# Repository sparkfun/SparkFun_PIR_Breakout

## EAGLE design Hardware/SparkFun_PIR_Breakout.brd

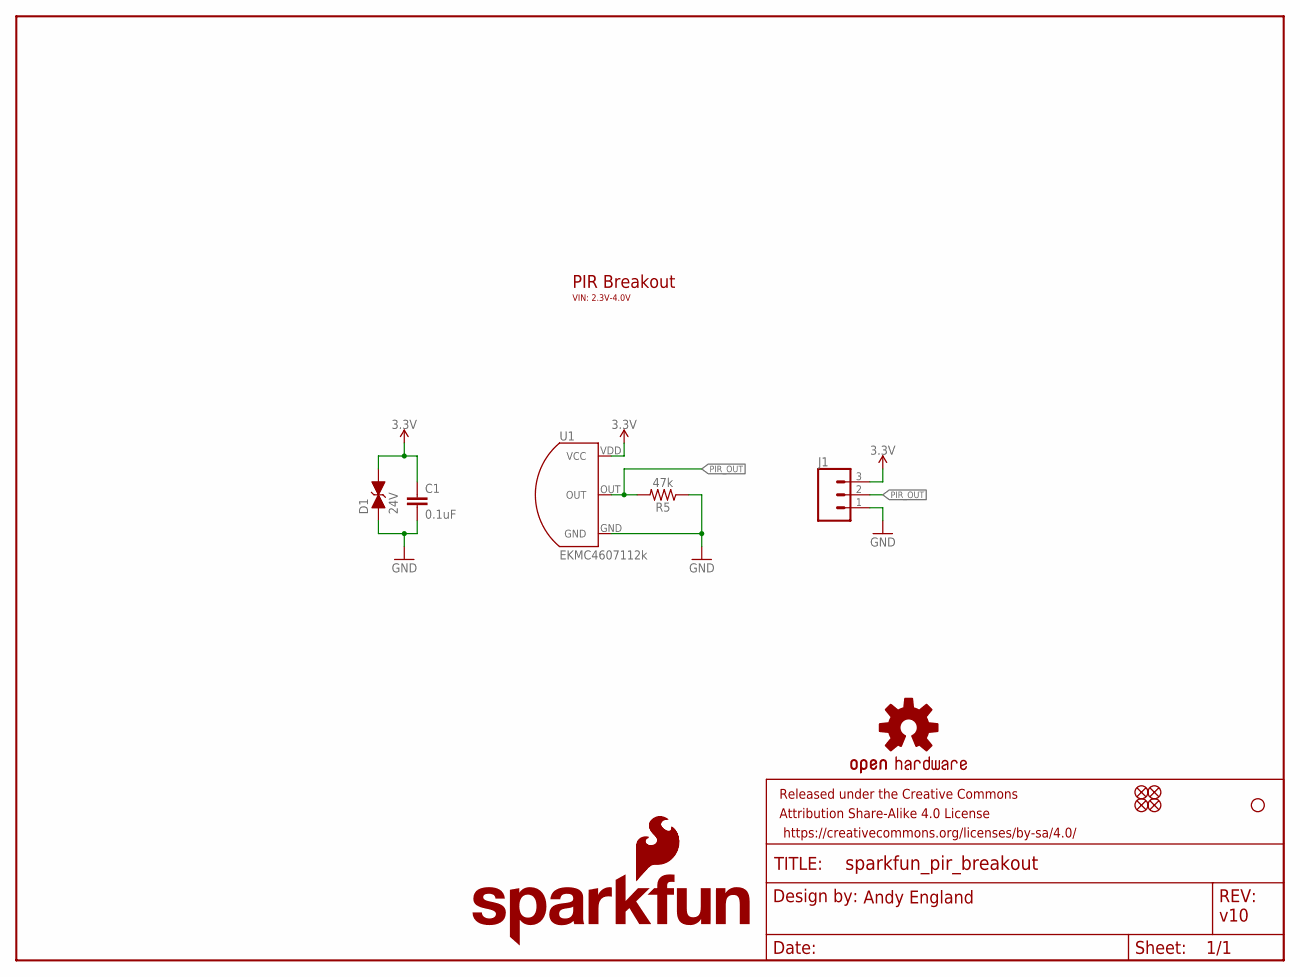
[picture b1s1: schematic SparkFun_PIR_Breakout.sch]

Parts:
C1: 0.1uF; 0603
D1: 24V; 0603
FRAME1: FRAME-LETTER; CREATIVE_COMMONS
H1: STAND-OFF
J1: CONN_031X03_NO_SILK; 1X03_NO_SILK
JP2, JP6, JP8, JP9: FIDUCIALUFIDUCIAL; MICRO-FIDUCIAL
LOGO1: OSHW-LOGOMINI; OSHW-LOGO-MINI
LOGO3: SFE_LOGO_NAME_FLAME.1_INCH; SFE_LOGO_NAME_FLAME_.1
LOGO4: SFE_LOGO_FLAME.1_INCH; SFE_LOGO_FLAME_.1
R5: 47k; 0603
U1: EKMC4607112k; TO-3

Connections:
3.3V: C1.1, D1.2 (C), J1.3, U1.VDD (VCC)
GND: C1.2, D1.1 (A), J1.1, R5.1, U1.GND
PIR_OUT: J1.2, R5.2, U1.OUT

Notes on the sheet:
v10
Andy England
PIR Breakout
VIN: 2.3V-4.0V

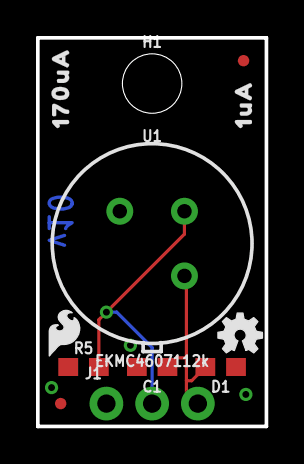
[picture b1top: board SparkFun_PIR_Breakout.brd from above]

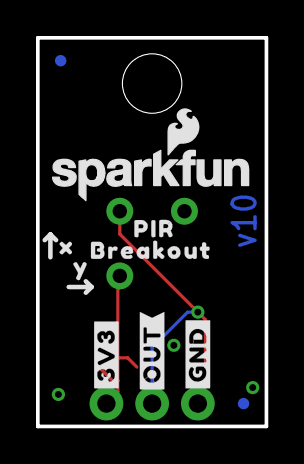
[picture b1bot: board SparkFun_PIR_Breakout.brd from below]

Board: 2 copper layers, 12.7 x 21.6 mm, 23 parts (10 on the bottom side), 3 nets.

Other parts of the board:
U$1: #3V3#0
U$2: 170UA0
U$3: #GND#0
U$9: 1UA0
U$11: #OUT#0
U$12: BREAKOUT0
U$13: PIR0
U$14: X0
U$16: Y0

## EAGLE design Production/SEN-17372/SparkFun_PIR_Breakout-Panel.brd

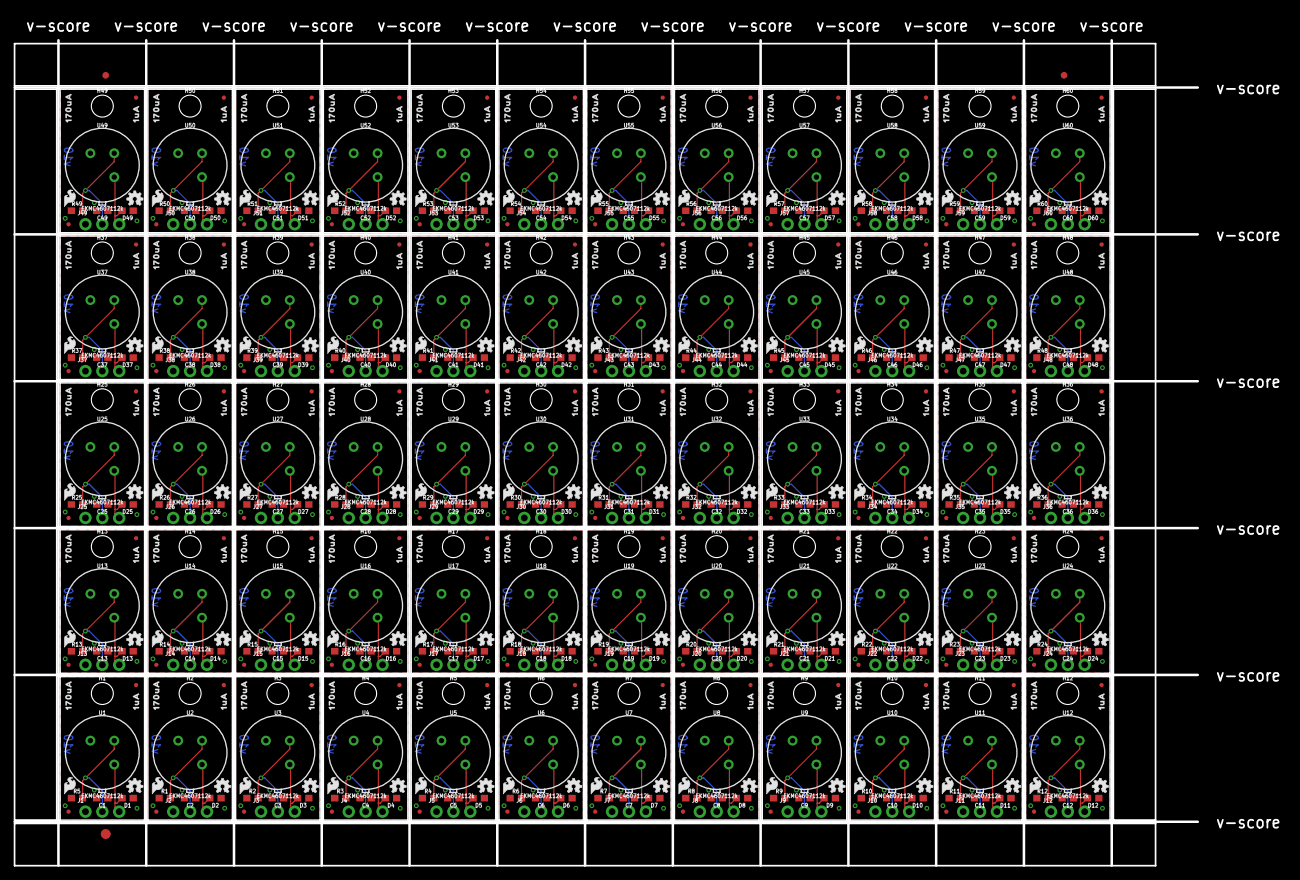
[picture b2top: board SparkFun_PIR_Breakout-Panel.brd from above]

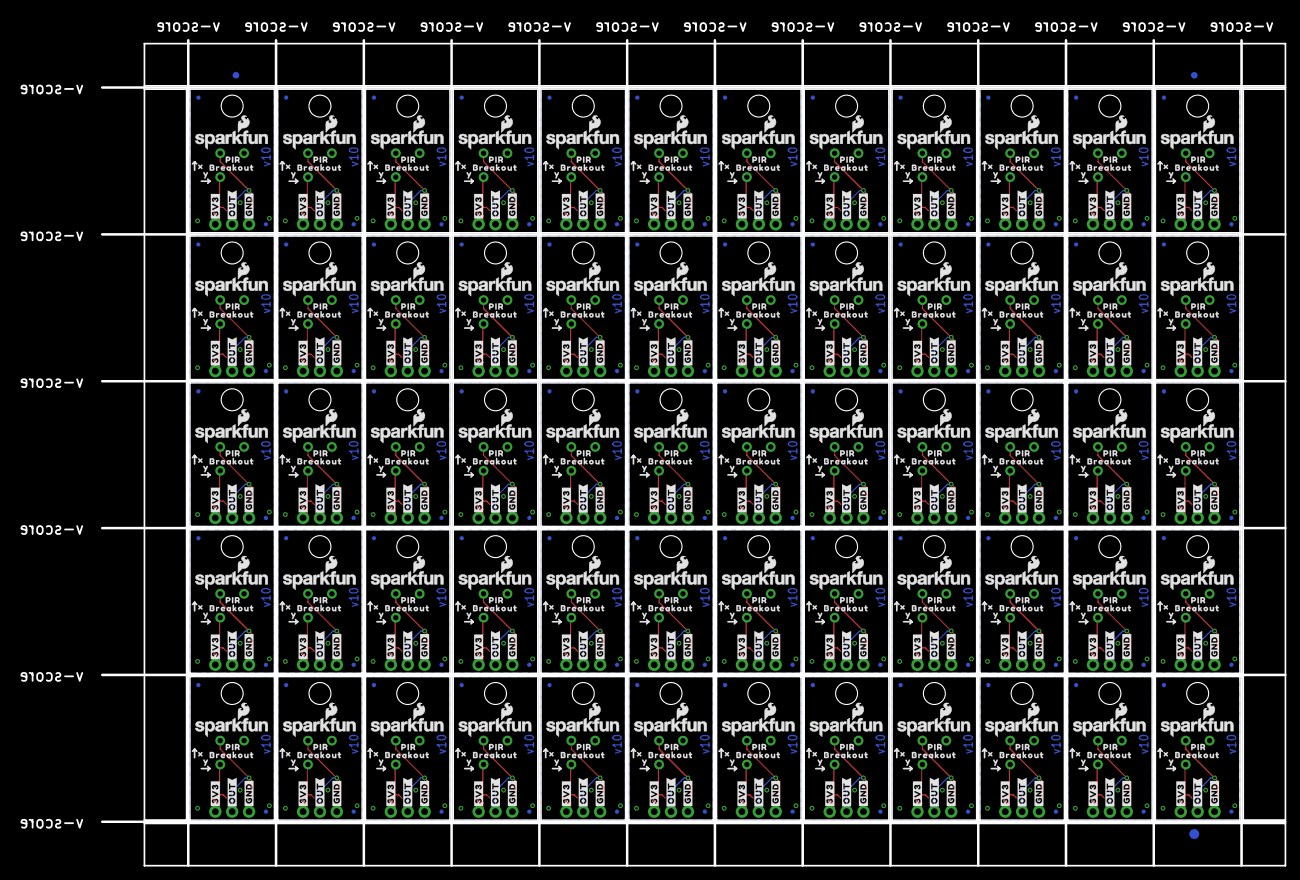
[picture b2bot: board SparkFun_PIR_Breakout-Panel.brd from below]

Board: 2 copper layers, 191.2 x 128.1 mm, 1326 parts (603 on the bottom side), 180 nets.

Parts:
C1, C2, C3, C4, C5, C6, C7, C8, C9, C10, C11, C12, C13, C14, C15, C16, C17, C18, C19, C20, C21, C22, C23, C24, C25, C26, C27, C28, C29, C30, C31, C32, C33, C34, C35, C36, C37, C38, C39, C40, C41, C42, C43, C44, C45, C46, C47, C48, C49, C50, C51, C52, C53, C54, C55, C56, C57, C58, C59, C60: 0.1uF; 0603
D1, D2, D3, D4, D5, D6, D7, D8, D9, D10, D11, D12, D13, D14, D15, D16, D17, D18, D19, D20, D21, D22, D23, D24, D25, D26, D27, D28, D29, D30, D31, D32, D33, D34, D35, D36, D37, D38, D39, D40, D41, D42, D43, D44, D45, D46, D47, D48, D49, D50, D51, D52, D53, D54, D55, D56, D57, D58, D59, D60: 24V; 0603
E$1, E$2, E$3, E$4: FIDUCIAL-1X2
E$5, E$6: FIDUCIAL-1.5X3
H1, H2, H3, H4, H5, H6, H7, H8, H9, H10, H11, H12, H13, H14, H15, H16, H17, H18, H19, H20, H21, H22, H23, H24, H25, H26, H27, H28, H29, H30, H31, H32, H33, H34, H35, H36, H37, H38, H39, H40, H41, H42, H43, H44, H45, H46, H47, H48, H49, H50, H51, H52, H53, H54, H55, H56, H57, H58, H59, H60: STAND-OFF
J1, J2, J3, J4, J5, J6, J7, J8, J9, J10, J11, J12, J13, J14, J15, J16, J17, J18, J19, J20, J21, J22, J23, J24, J25, J26, J27, J28, J29, J30, J31, J32, J33, J34, J35, J36, J37, J38, J39, J40, J41, J42, J43, J44, J45, J46, J47, J48, J49, J50, J51, J52, J53, J54, J55, J56, J57, J58, J59, J60: 1X03_NO_SILK
JP1, JP2, JP3, JP4, JP5, JP6, JP7, JP8, JP9, JP10, JP11, JP12, JP13, JP14, JP15, JP16, JP17, JP18, JP19, JP20, JP21, JP22, JP23, JP24, JP25, JP26, JP27, JP28, JP29, JP30, JP31, JP32, JP33, JP34, JP35, JP36, JP37, JP38, JP39, JP40, JP41, JP42, JP43, JP44, JP45, JP46, JP47, JP48, JP49, JP50, JP51, JP52, JP53, JP54, JP55, JP56, JP57, JP58, JP59, JP60, JP61, JP62, JP63, JP64, JP65, JP66, JP67, JP68, JP69, JP70, JP71, JP72, JP73, JP74, JP75, JP76, JP77, JP78, JP79, JP80, JP81, JP82, JP83, JP84, JP85, JP86, JP87, JP88, JP89, JP90, JP91, JP92, JP93, JP94, JP95, JP96, JP97, JP98, JP99, JP100, JP101, JP102, JP103, JP104, JP105, JP106, JP107, JP108, JP109, JP110, JP111, JP112, JP113, JP114, JP115, JP116, JP117, JP118, JP119, JP120, JP121, JP122, JP123, JP124, JP125, JP126, JP127, JP128, JP129, JP130, JP131, JP132, JP133, JP134, JP135, JP136, JP137, JP138, JP139, JP140, JP141, JP142, JP143, JP144, JP145, JP146, JP147, JP148, JP149, JP150, JP151, JP152, JP153, JP154, JP155, JP156, JP157, JP158, JP159, JP160, JP161, JP162, JP163, JP164, JP165, JP166, JP167, JP168, JP169, JP170, JP171, JP172, JP173, JP174, JP175, JP176, JP177, JP178, JP179, JP180, JP181, JP182, JP183, JP184, JP185, JP186, JP187, JP188, JP189, JP190, JP191, JP192, JP193, JP194, JP195, JP196, JP197, JP198, JP199, JP200, JP201, JP202, JP203, JP204, JP205, JP206, JP207, JP208, JP209, JP210, JP211, JP212, JP213, JP214, JP215, JP216, JP217, JP218, JP219, JP220, JP221, JP222, JP223, JP224, JP225, JP226, JP227, JP228, JP229, JP230, JP231, JP232, JP233, JP234, JP235, JP236, JP237, JP238, JP239, JP240: FIDUCIALUFIDUCIAL; MICRO-FIDUCIAL
LOGO1, LOGO2, LOGO7, LOGO10, LOGO13, LOGO16, LOGO19, LOGO22, LOGO25, LOGO28, LOGO31, LOGO34, LOGO37, LOGO40, LOGO43, LOGO46, LOGO49, LOGO52, LOGO55, LOGO58, LOGO61, LOGO64, LOGO67, LOGO70, LOGO73, LOGO76, LOGO79, LOGO82, LOGO85, LOGO88, LOGO91, LOGO94, LOGO97, LOGO100, LOGO103, LOGO106, LOGO109, LOGO112, LOGO115, LOGO118, LOGO121, LOGO124, LOGO127, LOGO130, LOGO133, LOGO136, LOGO139, LOGO142, LOGO145, LOGO148, LOGO151, LOGO154, LOGO157, LOGO160, LOGO163, LOGO166, LOGO169, LOGO172, LOGO175, LOGO178: OSHW-LOGOMINI; OSHW-LOGO-MINI
LOGO3, LOGO5, LOGO8, LOGO11, LOGO14, LOGO17, LOGO20, LOGO23, LOGO26, LOGO29, LOGO32, LOGO35, LOGO38, LOGO41, LOGO44, LOGO47, LOGO50, LOGO53, LOGO56, LOGO59, LOGO62, LOGO65, LOGO68, LOGO71, LOGO74, LOGO77, LOGO80, LOGO83, LOGO86, LOGO89, LOGO92, LOGO95, LOGO98, LOGO101, LOGO104, LOGO107, LOGO110, LOGO113, LOGO116, LOGO119, LOGO122, LOGO125, LOGO128, LOGO131, LOGO134, LOGO137, LOGO140, LOGO143, LOGO146, LOGO149, LOGO152, LOGO155, LOGO158, LOGO161, LOGO164, LOGO167, LOGO170, LOGO173, LOGO176, LOGO179: SFE_LOGO_NAME_FLAME.1_INCH; SFE_LOGO_NAME_FLAME_.1
LOGO4, LOGO6, LOGO9, LOGO12, LOGO15, LOGO18, LOGO21, LOGO24, LOGO27, LOGO30, LOGO33, LOGO36, LOGO39, LOGO42, LOGO45, LOGO48, LOGO51, LOGO54, LOGO57, LOGO60, LOGO63, LOGO66, LOGO69, LOGO72, LOGO75, LOGO78, LOGO81, LOGO84, LOGO87, LOGO90, LOGO93, LOGO96, LOGO99, LOGO102, LOGO105, LOGO108, LOGO111, LOGO114, LOGO117, LOGO120, LOGO123, LOGO126, LOGO129, LOGO132, LOGO135, LOGO138, LOGO141, LOGO144, LOGO147, LOGO150, LOGO153, LOGO156, LOGO159, LOGO162, LOGO165, LOGO168, LOGO171, LOGO174, LOGO177, LOGO180: SFE_LOGO_FLAME.1_INCH; SFE_LOGO_FLAME_.1
R1, R2, R3, R4, R5, R6, R7, R8, R9, R10, R11, R12, R13, R14, R15, R16, R17, R18, R19, R20, R21, R22, R23, R24, R25, R26, R27, R28, R29, R30, R31, R32, R33, R34, R35, R36, R37, R38, R39, R40, R41, R42, R43, R44, R45, R46, R47, R48, R49, R50, R51, R52, R53, R54, R55, R56, R57, R58, R59, R60: 47k; 0603
U1, U2, U3, U4, U5, U6, U7, U8, U9, U10, U11, U12, U13, U14, U15, U16, U17, U18, U19, U20, U21, U22, U23, U24, U25, U26, U27, U28, U29, U30, U31, U32, U33, U34, U35, U36, U37, U38, U39, U40, U41, U42, U43, U44, U45, U46, U47, U48, U49, U50, U51, U52, U53, U54, U55, U56, U57, U58, U59, U60: EKMC4607112k; TO-3
U$1, U$10, U$24, U$33, U$42, U$51, U$60, U$69, U$78, U$87, U$96, U$105, U$114, U$123, U$132, U$141, U$150, U$159, U$168, U$177, U$186, U$195, U$204, U$213, U$222, U$231, U$240, U$249, U$258, U$267, U$276, U$285, U$294, U$303, U$312, U$321, U$330, U$339, U$348, U$357, U$366, U$375, U$384, U$393, U$402, U$411, U$420, U$429, U$438, U$447, U$456, U$465, U$474, U$483, U$492, U$501, U$510, U$519, U$528, U$537: #3V3#0
U$2, U$5, U$20, U$29, U$38, U$47, U$56, U$65, U$74, U$83, U$92, U$101, U$110, U$119, U$128, U$137, U$146, U$155, U$164, U$173, U$182, U$191, U$200, U$209, U$218, U$227, U$236, U$245, U$254, U$263, U$272, U$281, U$290, U$299, U$308, U$317, U$326, U$335, U$344, U$353, U$362, U$371, U$380, U$389, U$398, U$407, U$416, U$425, U$434, U$443, U$452, U$461, U$470, U$479, U$488, U$497, U$506, U$515, U$524, U$533: 170UA0
U$3, U$15, U$25, U$34, U$43, U$52, U$61, U$70, U$79, U$88, U$97, U$106, U$115, U$124, U$133, U$142, U$151, U$160, U$169, U$178, U$187, U$196, U$205, U$214, U$223, U$232, U$241, U$250, U$259, U$268, U$277, U$286, U$295, U$304, U$313, U$322, U$331, U$340, U$349, U$358, U$367, U$376, U$385, U$394, U$403, U$412, U$421, U$430, U$439, U$448, U$457, U$466, U$475, U$484, U$493, U$502, U$511, U$520, U$529, U$538: #GND#0
U$4, U$13, U$19, U$28, U$37, U$46, U$55, U$64, U$73, U$82, U$91, U$100, U$109, U$118, U$127, U$136, U$145, U$154, U$163, U$172, U$181, U$190, U$199, U$208, U$217, U$226, U$235, U$244, U$253, U$262, U$271, U$280, U$289, U$298, U$307, U$316, U$325, U$334, U$343, U$352, U$361, U$370, U$379, U$388, U$397, U$406, U$415, U$424, U$433, U$442, U$451, U$460, U$469, U$478, U$487, U$496, U$505, U$514, U$523, U$532: PIR0
U$6, U$9, U$21, U$30, U$39, U$48, U$57, U$66, U$75, U$84, U$93, U$102, U$111, U$120, U$129, U$138, U$147, U$156, U$165, U$174, U$183, U$192, U$201, U$210, U$219, U$228, U$237, U$246, U$255, U$264, U$273, U$282, U$291, U$300, U$309, U$318, U$327, U$336, U$345, U$354, U$363, U$372, U$381, U$390, U$399, U$408, U$417, U$426, U$435, U$444, U$453, U$462, U$471, U$480, U$489, U$498, U$507, U$516, U$525, U$534: 1UA0
U$7, U$12, U$22, U$31, U$40, U$49, U$58, U$67, U$76, U$85, U$94, U$103, U$112, U$121, U$130, U$139, U$148, U$157, U$166, U$175, U$184, U$193, U$202, U$211, U$220, U$229, U$238, U$247, U$256, U$265, U$274, U$283, U$292, U$301, U$310, U$319, U$328, U$337, U$346, U$355, U$364, U$373, U$382, U$391, U$400, U$409, U$418, U$427, U$436, U$445, U$454, U$463, U$472, U$481, U$490, U$499, U$508, U$517, U$526, U$535: BREAKOUT0
U$8, U$11, U$23, U$32, U$41, U$50, U$59, U$68, U$77, U$86, U$95, U$104, U$113, U$122, U$131, U$140, U$149, U$158, U$167, U$176, U$185, U$194, U$203, U$212, U$221, U$230, U$239, U$248, U$257, U$266, U$275, U$284, U$293, U$302, U$311, U$320, U$329, U$338, U$347, U$356, U$365, U$374, U$383, U$392, U$401, U$410, U$419, U$428, U$437, U$446, U$455, U$464, U$473, U$482, U$491, U$500, U$509, U$518, U$527, U$536: #OUT#0
U$14, U$17, U$26, U$35, U$44, U$53, U$62, U$71, U$80, U$89, U$98, U$107, U$116, U$125, U$134, U$143, U$152, U$161, U$170, U$179, U$188, U$197, U$206, U$215, U$224, U$233, U$242, U$251, U$260, U$269, U$278, U$287, U$296, U$305, U$314, U$323, U$332, U$341, U$350, U$359, U$368, U$377, U$386, U$395, U$404, U$413, U$422, U$431, U$440, U$449, U$458, U$467, U$476, U$485, U$494, U$503, U$512, U$521, U$530, U$539: X0
U$16, U$18, U$27, U$36, U$45, U$54, U$63, U$72, U$81, U$90, U$99, U$108, U$117, U$126, U$135, U$144, U$153, U$162, U$171, U$180, U$189, U$198, U$207, U$216, U$225, U$234, U$243, U$252, U$261, U$270, U$279, U$288, U$297, U$306, U$315, U$324, U$333, U$342, U$351, U$360, U$369, U$378, U$387, U$396, U$405, U$414, U$423, U$432, U$441, U$450, U$459, U$468, U$477, U$486, U$495, U$504, U$513, U$522, U$531, U$540: Y0

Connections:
3.3V: C1.1, D1.2, J1.3, U1.VDD
3.3V1: C2.1, D2.2, J2.3, U2.VDD
3.3V2: C3.1, D3.2, J3.3, U3.VDD
3.3V3: C4.1, D4.2, J4.3, U4.VDD
3.3V4: C5.1, D5.2, J5.3, U5.VDD
3.3V5: C6.1, D6.2, J6.3, U6.VDD
3.3V6: C7.1, D7.2, J7.3, U7.VDD
3.3V7: C8.1, D8.2, J8.3, U8.VDD
3.3V8: C9.1, D9.2, J9.3, U9.VDD
3.3V9: C10.1, D10.2, J10.3, U10.VDD
3.3V10: C11.1, D11.2, J11.3, U11.VDD
3.3V11: C12.1, D12.2, J12.3, U12.VDD
3.3V12: C13.1, D13.2, J13.3, U13.VDD
3.3V13: C14.1, D14.2, J14.3, U14.VDD
3.3V14: C15.1, D15.2, J15.3, U15.VDD
3.3V15: C16.1, D16.2, J16.3, U16.VDD
3.3V16: C17.1, D17.2, J17.3, U17.VDD
3.3V17: C18.1, D18.2, J18.3, U18.VDD
3.3V18: C19.1, D19.2, J19.3, U19.VDD
3.3V19: C20.1, D20.2, J20.3, U20.VDD
3.3V20: C21.1, D21.2, J21.3, U21.VDD
3.3V21: C22.1, D22.2, J22.3, U22.VDD
3.3V22: C23.1, D23.2, J23.3, U23.VDD
3.3V23: C24.1, D24.2, J24.3, U24.VDD
3.3V24: C25.1, D25.2, J25.3, U25.VDD
3.3V25: C26.1, D26.2, J26.3, U26.VDD
3.3V26: C27.1, D27.2, J27.3, U27.VDD
3.3V27: C28.1, D28.2, J28.3, U28.VDD
3.3V28: C29.1, D29.2, J29.3, U29.VDD
3.3V29: C30.1, D30.2, J30.3, U30.VDD
3.3V30: C31.1, D31.2, J31.3, U31.VDD
3.3V31: C32.1, D32.2, J32.3, U32.VDD
3.3V32: C33.1, D33.2, J33.3, U33.VDD
3.3V33: C34.1, D34.2, J34.3, U34.VDD
3.3V34: C35.1, D35.2, J35.3, U35.VDD
3.3V35: C36.1, D36.2, J36.3, U36.VDD
3.3V36: C37.1, D37.2, J37.3, U37.VDD
3.3V37: C38.1, D38.2, J38.3, U38.VDD
3.3V38: C39.1, D39.2, J39.3, U39.VDD
3.3V39: C40.1, D40.2, J40.3, U40.VDD
3.3V40: C41.1, D41.2, J41.3, U41.VDD
3.3V41: C42.1, D42.2, J42.3, U42.VDD
3.3V42: C43.1, D43.2, J43.3, U43.VDD
3.3V43: C44.1, D44.2, J44.3, U44.VDD
3.3V44: C45.1, D45.2, J45.3, U45.VDD
3.3V45: C46.1, D46.2, J46.3, U46.VDD
3.3V46: C47.1, D47.2, J47.3, U47.VDD
3.3V47: C48.1, D48.2, J48.3, U48.VDD
3.3V48: C49.1, D49.2, J49.3, U49.VDD
3.3V49: C50.1, D50.2, J50.3, U50.VDD
3.3V50: C51.1, D51.2, J51.3, U51.VDD
3.3V51: C52.1, D52.2, J52.3, U52.VDD
3.3V52: C53.1, D53.2, J53.3, U53.VDD
3.3V53: C54.1, D54.2, J54.3, U54.VDD
3.3V54: C55.1, D55.2, J55.3, U55.VDD
3.3V55: C56.1, D56.2, J56.3, U56.VDD
3.3V56: C57.1, D57.2, J57.3, U57.VDD
3.3V57: C58.1, D58.2, J58.3, U58.VDD
3.3V58: C59.1, D59.2, J59.3, U59.VDD
3.3V59: C60.1, D60.2, J60.3, U60.VDD
GND: C1.2, D1.1, J1.1, R5.1, U1.GND
GND1: C2.2, D2.1, J2.1, R1.1, U2.GND
GND2: C3.2, D3.1, J3.1, R2.1, U3.GND
GND3: C4.2, D4.1, J4.1, R3.1, U4.GND
GND4: C5.2, D5.1, J5.1, R4.1, U5.GND
GND5: C6.2, D6.1, J6.1, R6.1, U6.GND
GND6: C7.2, D7.1, J7.1, R7.1, U7.GND
GND7: C8.2, D8.1, J8.1, R8.1, U8.GND
GND8: C9.2, D9.1, J9.1, R9.1, U9.GND
GND9: C10.2, D10.1, J10.1, R10.1, U10.GND
GND10: C11.2, D11.1, J11.1, R11.1, U11.GND
GND11: C12.2, D12.1, J12.1, R12.1, U12.GND
GND12: C13.2, D13.1, J13.1, R13.1, U13.GND
GND13: C14.2, D14.1, J14.1, R14.1, U14.GND
GND14: C15.2, D15.1, J15.1, R15.1, U15.GND
GND15: C16.2, D16.1, J16.1, R16.1, U16.GND
GND16: C17.2, D17.1, J17.1, R17.1, U17.GND
GND17: C18.2, D18.1, J18.1, R18.1, U18.GND
GND18: C19.2, D19.1, J19.1, R19.1, U19.GND
GND19: C20.2, D20.1, J20.1, R20.1, U20.GND
GND20: C21.2, D21.1, J21.1, R21.1, U21.GND
GND21: C22.2, D22.1, J22.1, R22.1, U22.GND
GND22: C23.2, D23.1, J23.1, R23.1, U23.GND
GND23: C24.2, D24.1, J24.1, R24.1, U24.GND
GND24: C25.2, D25.1, J25.1, R25.1, U25.GND
GND25: C26.2, D26.1, J26.1, R26.1, U26.GND
GND26: C27.2, D27.1, J27.1, R27.1, U27.GND
GND27: C28.2, D28.1, J28.1, R28.1, U28.GND
GND28: C29.2, D29.1, J29.1, R29.1, U29.GND
GND29: C30.2, D30.1, J30.1, R30.1, U30.GND
GND30: C31.2, D31.1, J31.1, R31.1, U31.GND
GND31: C32.2, D32.1, J32.1, R32.1, U32.GND
GND32: C33.2, D33.1, J33.1, R33.1, U33.GND
GND33: C34.2, D34.1, J34.1, R34.1, U34.GND
GND34: C35.2, D35.1, J35.1, R35.1, U35.GND
GND35: C36.2, D36.1, J36.1, R36.1, U36.GND
GND36: C37.2, D37.1, J37.1, R37.1, U37.GND
GND37: C38.2, D38.1, J38.1, R38.1, U38.GND
GND38: C39.2, D39.1, J39.1, R39.1, U39.GND
GND39: C40.2, D40.1, J40.1, R40.1, U40.GND
GND40: C41.2, D41.1, J41.1, R41.1, U41.GND
GND41: C42.2, D42.1, J42.1, R42.1, U42.GND
GND42: C43.2, D43.1, J43.1, R43.1, U43.GND
GND43: C44.2, D44.1, J44.1, R44.1, U44.GND
GND44: C45.2, D45.1, J45.1, R45.1, U45.GND
GND45: C46.2, D46.1, J46.1, R46.1, U46.GND
GND46: C47.2, D47.1, J47.1, R47.1, U47.GND
GND47: C48.2, D48.1, J48.1, R48.1, U48.GND
GND48: C49.2, D49.1, J49.1, R49.1, U49.GND
GND49: C50.2, D50.1, J50.1, R50.1, U50.GND
GND50: C51.2, D51.1, J51.1, R51.1, U51.GND
GND51: C52.2, D52.1, J52.1, R52.1, U52.GND
GND52: C53.2, D53.1, J53.1, R53.1, U53.GND
GND53: C54.2, D54.1, J54.1, R54.1, U54.GND
GND54: C55.2, D55.1, J55.1, R55.1, U55.GND
GND55: C56.2, D56.1, J56.1, R56.1, U56.GND
GND56: C57.2, D57.1, J57.1, R57.1, U57.GND
GND57: C58.2, D58.1, J58.1, R58.1, U58.GND
GND58: C59.2, D59.1, J59.1, R59.1, U59.GND
GND59: C60.2, D60.1, J60.1, R60.1, U60.GND
PIR_OUT: J1.2, R5.2, U1.OUT
PIR_OUT1: J2.2, R1.2, U2.OUT
PIR_OUT2: J3.2, R2.2, U3.OUT
PIR_OUT3: J4.2, R3.2, U4.OUT
PIR_OUT4: J5.2, R4.2, U5.OUT
PIR_OUT5: J6.2, R6.2, U6.OUT
PIR_OUT6: J7.2, R7.2, U7.OUT
PIR_OUT7: J8.2, R8.2, U8.OUT
PIR_OUT8: J9.2, R9.2, U9.OUT
PIR_OUT9: J10.2, R10.2, U10.OUT
PIR_OUT10: J11.2, R11.2, U11.OUT
PIR_OUT11: J12.2, R12.2, U12.OUT
PIR_OUT12: J13.2, R13.2, U13.OUT
PIR_OUT13: J14.2, R14.2, U14.OUT
PIR_OUT14: J15.2, R15.2, U15.OUT
PIR_OUT15: J16.2, R16.2, U16.OUT
PIR_OUT16: J17.2, R17.2, U17.OUT
PIR_OUT17: J18.2, R18.2, U18.OUT
PIR_OUT18: J19.2, R19.2, U19.OUT
PIR_OUT19: J20.2, R20.2, U20.OUT
PIR_OUT20: J21.2, R21.2, U21.OUT
PIR_OUT21: J22.2, R22.2, U22.OUT
PIR_OUT22: J23.2, R23.2, U23.OUT
PIR_OUT23: J24.2, R24.2, U24.OUT
PIR_OUT24: J25.2, R25.2, U25.OUT
PIR_OUT25: J26.2, R26.2, U26.OUT
PIR_OUT26: J27.2, R27.2, U27.OUT
PIR_OUT27: J28.2, R28.2, U28.OUT
PIR_OUT28: J29.2, R29.2, U29.OUT
PIR_OUT29: J30.2, R30.2, U30.OUT
PIR_OUT30: J31.2, R31.2, U31.OUT
PIR_OUT31: J32.2, R32.2, U32.OUT
PIR_OUT32: J33.2, R33.2, U33.OUT
PIR_OUT33: J34.2, R34.2, U34.OUT
PIR_OUT34: J35.2, R35.2, U35.OUT
PIR_OUT35: J36.2, R36.2, U36.OUT
PIR_OUT36: J37.2, R37.2, U37.OUT
PIR_OUT37: J38.2, R38.2, U38.OUT
PIR_OUT38: J39.2, R39.2, U39.OUT
PIR_OUT39: J40.2, R40.2, U40.OUT
PIR_OUT40: J41.2, R41.2, U41.OUT
PIR_OUT41: J42.2, R42.2, U42.OUT
PIR_OUT42: J43.2, R43.2, U43.OUT
PIR_OUT43: J44.2, R44.2, U44.OUT
PIR_OUT44: J45.2, R45.2, U45.OUT
PIR_OUT45: J46.2, R46.2, U46.OUT
PIR_OUT46: J47.2, R47.2, U47.OUT
PIR_OUT47: J48.2, R48.2, U48.OUT
PIR_OUT48: J49.2, R49.2, U49.OUT
PIR_OUT49: J50.2, R50.2, U50.OUT
PIR_OUT50: J51.2, R51.2, U51.OUT
PIR_OUT51: J52.2, R52.2, U52.OUT
PIR_OUT52: J53.2, R53.2, U53.OUT
PIR_OUT53: J54.2, R54.2, U54.OUT
PIR_OUT54: J55.2, R55.2, U55.OUT
PIR_OUT55: J56.2, R56.2, U56.OUT
PIR_OUT56: J57.2, R57.2, U57.OUT
PIR_OUT57: J58.2, R58.2, U58.OUT
PIR_OUT58: J59.2, R59.2, U59.OUT
PIR_OUT59: J60.2, R60.2, U60.OUT

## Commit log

2020-10-07 post checklist changes
2020-10-07 checklist saved changes
2020-10-09 adding panel
2020-10-12 adding fiducial to panel
2020-10-12 removing fiducial
2020-10-12 downsizing panel
2020-10-21 adding panel for 1uA
2021-01-22 updating panel file
2021-01-27 Update README.md
    Updating README from repo template.

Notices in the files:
parts and their libraries:
SparkFun-Aesthetics: Licensing: Creative Commons ShareAlike 4.0 International - https://creativecommons.org/licenses/by-sa/4.0
SparkFun-Aesthetics: Released under the Creative Commons Attribution Share-Alike 4.0 License
SparkFun-Aesthetics: https://creativecommons.org/licenses/by-sa/4.0
